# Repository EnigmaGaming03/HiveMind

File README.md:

# HiveMind
Drone swarm system with ESP32's for o2o(Object to Object) Communication 
# HiveMind

## Distributed Modular UAV Swarm Platform

### Overview

HiveMind is a modular drone swarm platform designed around low-cost, open-source hardware. The system enables up to 10 autonomous drones to communicate, collaborate, and perform coordinated tasks such as environmental scanning, mapping, surveillance, search operations, and distributed sensing.

Each drone functions as an independent node equipped with an ESP32-CAM for onboard vision processing and wireless communication. Through inter-drone networking, HiveMind allows multiple UAVs to share information, distribute workloads, and build a collective understanding of their environment.

The project aims to bridge the gap between hobbyist drone systems and expensive enterprise swarm technologies by creating an affordable, scalable, and customizable platform.

## Key Features

### Swarm Networking

* Supports up to 10 interconnected drones
* Peer-to-peer communication architecture
* Distributed task allocation
* Real-time information sharing
* Redundant network paths for improved reliability

### Computer Vision

* ESP32-CAM based image acquisition
* Object detection and tracking capabilities
* Area scanning and monitoring
* Image sharing between swarm members
* Distributed visual coverage

### Modular Architecture

* Plug-and-play drone nodes
* Scalable swarm size
* Easily replaceable hardware modules
* Open-source hardware and software design

### Autonomous Operations

* Cooperative area exploration
* Multi-drone scanning missions
* Dynamic route assignment
* Collective mapping capabilities
* Distributed sensor fusion

---

## System Architecture

Each HiveMind node consists of:

### Flight System

* Flight controller
* Electronic speed controllers
* Brushless motors
* LiPo battery system

### Processing System

* ESP32-CAM
* Wireless communication module
* Onboard sensor interface

### Custom Motor Driver

HiveMind utilizes a custom-designed 4-channel motor driver featuring:

#### Components

* Q_NMOS MOSFETs
* 4S4148 switching diodes
* 10 kΩ gate resistors

#### Features

* Compact design
* Low-cost implementation
* Efficient motor switching
* Suitable for lightweight UAV applications
* Fully customizable PCB layout

---

## Communication Framework

The HiveMind network operates as a distributed swarm where each drone acts as both a data source and relay node.

### Capabilities

* Position sharing
* Mission status updates
* Sensor data exchange
* Visual information sharing
* Dynamic task reassignment

### Swarm Functions

* Formation flying
* Collaborative mapping
* Search and rescue operations
* Area surveillance
* Environmental monitoring

---

## Potential Applications

### Search and Rescue

Multiple drones can rapidly scan large areas and identify points of interest while sharing findings across the swarm.

### Environmental Monitoring

Distributed sensors can collect data over larger regions than a single UAV could cover.

### Security and Surveillance

Swarm coverage provides increased situational awareness and redundancy.

### Research and Education

An affordable platform for studying:

* Swarm robotics
* Distributed systems
* Autonomous navigation
* Computer vision
* Multi-agent communication

---

## Project Goals

The primary goals of HiveMind are:

1. Develop an affordable swarm drone ecosystem.
2. Enable collaborative autonomous UAV operations.
3. Create an open-source research platform.
4. Demonstrate distributed intelligence using low-cost hardware.
5. Explore scalable swarm behaviors for real-world applications.

---

## Future Development

### Planned Features

* AI-assisted object recognition
* Autonomous path planning
* Mesh networking
* SLAM integration
* Distributed edge computing
* Ground control station software
* Swarm simulation environment
* Long-range communication modules
* Autonomous charging stations

---

## Project Status

Current Development Stage:

* Hardware architecture design
* Custom motor driver development
* ESP32-CAM integration
* Swarm communication framework planning

---

## License

This project is intended to be released under an open-source license to encourage collaboration, research, and community-driven development.

---

## Vision

HiveMind explores how simple, inexpensive autonomous drones can work together as a collective intelligence system, creating capabilities far beyond those of any individual aircraft.

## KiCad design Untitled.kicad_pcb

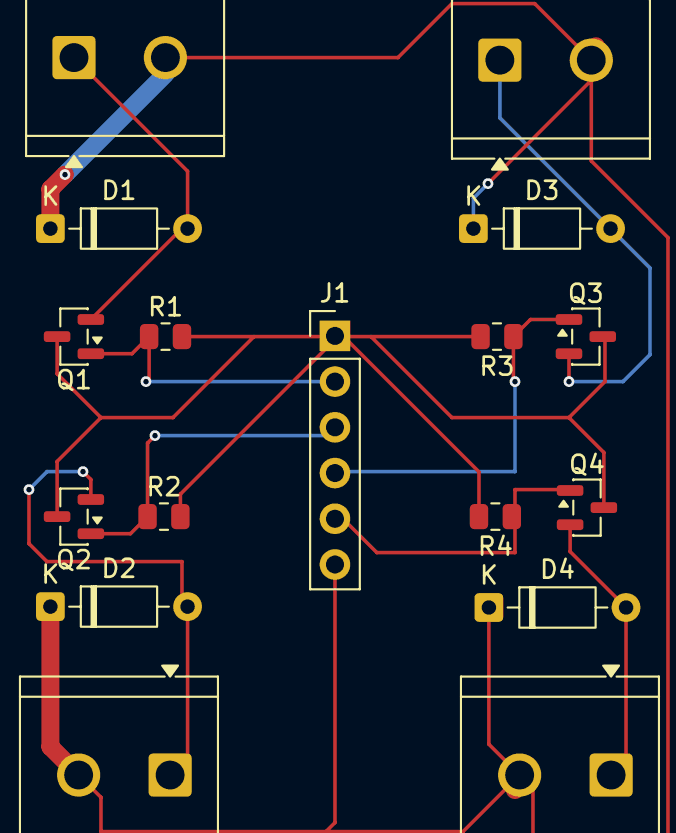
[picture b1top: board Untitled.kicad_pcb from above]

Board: 2 copper layers, 17 parts (0 on the bottom side), 10 nets.

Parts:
D1, D2, D3, D4: 1N4148; D_DO-35_SOD27_P7.62mm_Horizontal
J1: Conn_01x06_Pin; PinHeader_1x06_P2.54mm_Vertical
J2, J3, J4, J5: Screw_Terminal_01x02; TerminalBlock_CUI_TB007-508-02_1x02_P5.08mm_Horizontal
Q1, Q2, Q3, Q4: Q_NMOS; SOT-23
R1, R2, R3, R4: 10K; R_0805_2012Metric

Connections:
+5V: D1.1 (K), D2.1 (K), D3.1 (K), D4.1 (K), J1.6, J2.2, J3.2, J4.2, J5.2
/IN1: J1.2, R1.1
/IN2: J1.3, R2.1
/IN3: J1.4, R3.1
/IN4: J1.5, R4.1
GND: J1.1, R1.2, R2.2, R3.2, R4.2
unnamed: D1.2 (A), J2.1
unnamed: D2.2 (A), J3.1
unnamed: D3.2 (A), J4.1
unnamed: D4.2 (A), J5.1

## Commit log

2026-06-06 Enhance README with comprehensive project details
    Expanded the README to include detailed project overview, key features, system architecture, communication framework, potential applications, project goals, future development plans, and project stat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
2026-06-12 HiveMind_Sim_replit_prompt
    Developed a comprehensive web application for simulating ESP32-based node networks, including features for node management, command input, and network visualization.
